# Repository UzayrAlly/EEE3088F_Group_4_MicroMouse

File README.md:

# EEE3088F_Group_4_MicroMouse
Micro-Mouse Sensing Subsystem

This repository contains the design documentation and testing procedures for the sensing subsystem of the Micro-Mouse project. The sensing subsystem serves as the "eyes" of the Micro-Mouse, detecting walls within a maze environment using infrared light and providing signals for navigation.

Contents:

Design Decisions: Discusses the initial circuit design, component selection, evaluation, and final design of the sensing module. It outlines the rationale behind component choices and design modifications.
Failure Management: Describes the processes implemented for failure management in PCB design, including Electrical Rule Check (ERC), Design Rule Check (DRC), Design for Manufacturing (DFM), troubleshooting design, and circuit testing.
System Integration and Interfacing: Details the interfacing specifications and connections of the sensing subsystem with other components of the Micro-Mouse project. Includes an interfacing diagram and table describing the connections.
Acceptance Testing: Provides a comprehensive overview of acceptance tests conducted to verify that all components function as expected and meet requirements and specifications. Each test is described along with its testing procedure and pass/fail criteria.

Repository Structure:

Data sheets: data sheets for components.
Schematics: Includes schematic diagrams of the initial and final circuit designs for the sensing module.
PCB production files: includes items needed to manufacture the board

Usage:

This repository serves as a reference for understanding the design and testing procedures of the Micro-Mouse sensing subsystem. Developers and engineers can utilize the documentation and schematics for further development or troubleshooting.

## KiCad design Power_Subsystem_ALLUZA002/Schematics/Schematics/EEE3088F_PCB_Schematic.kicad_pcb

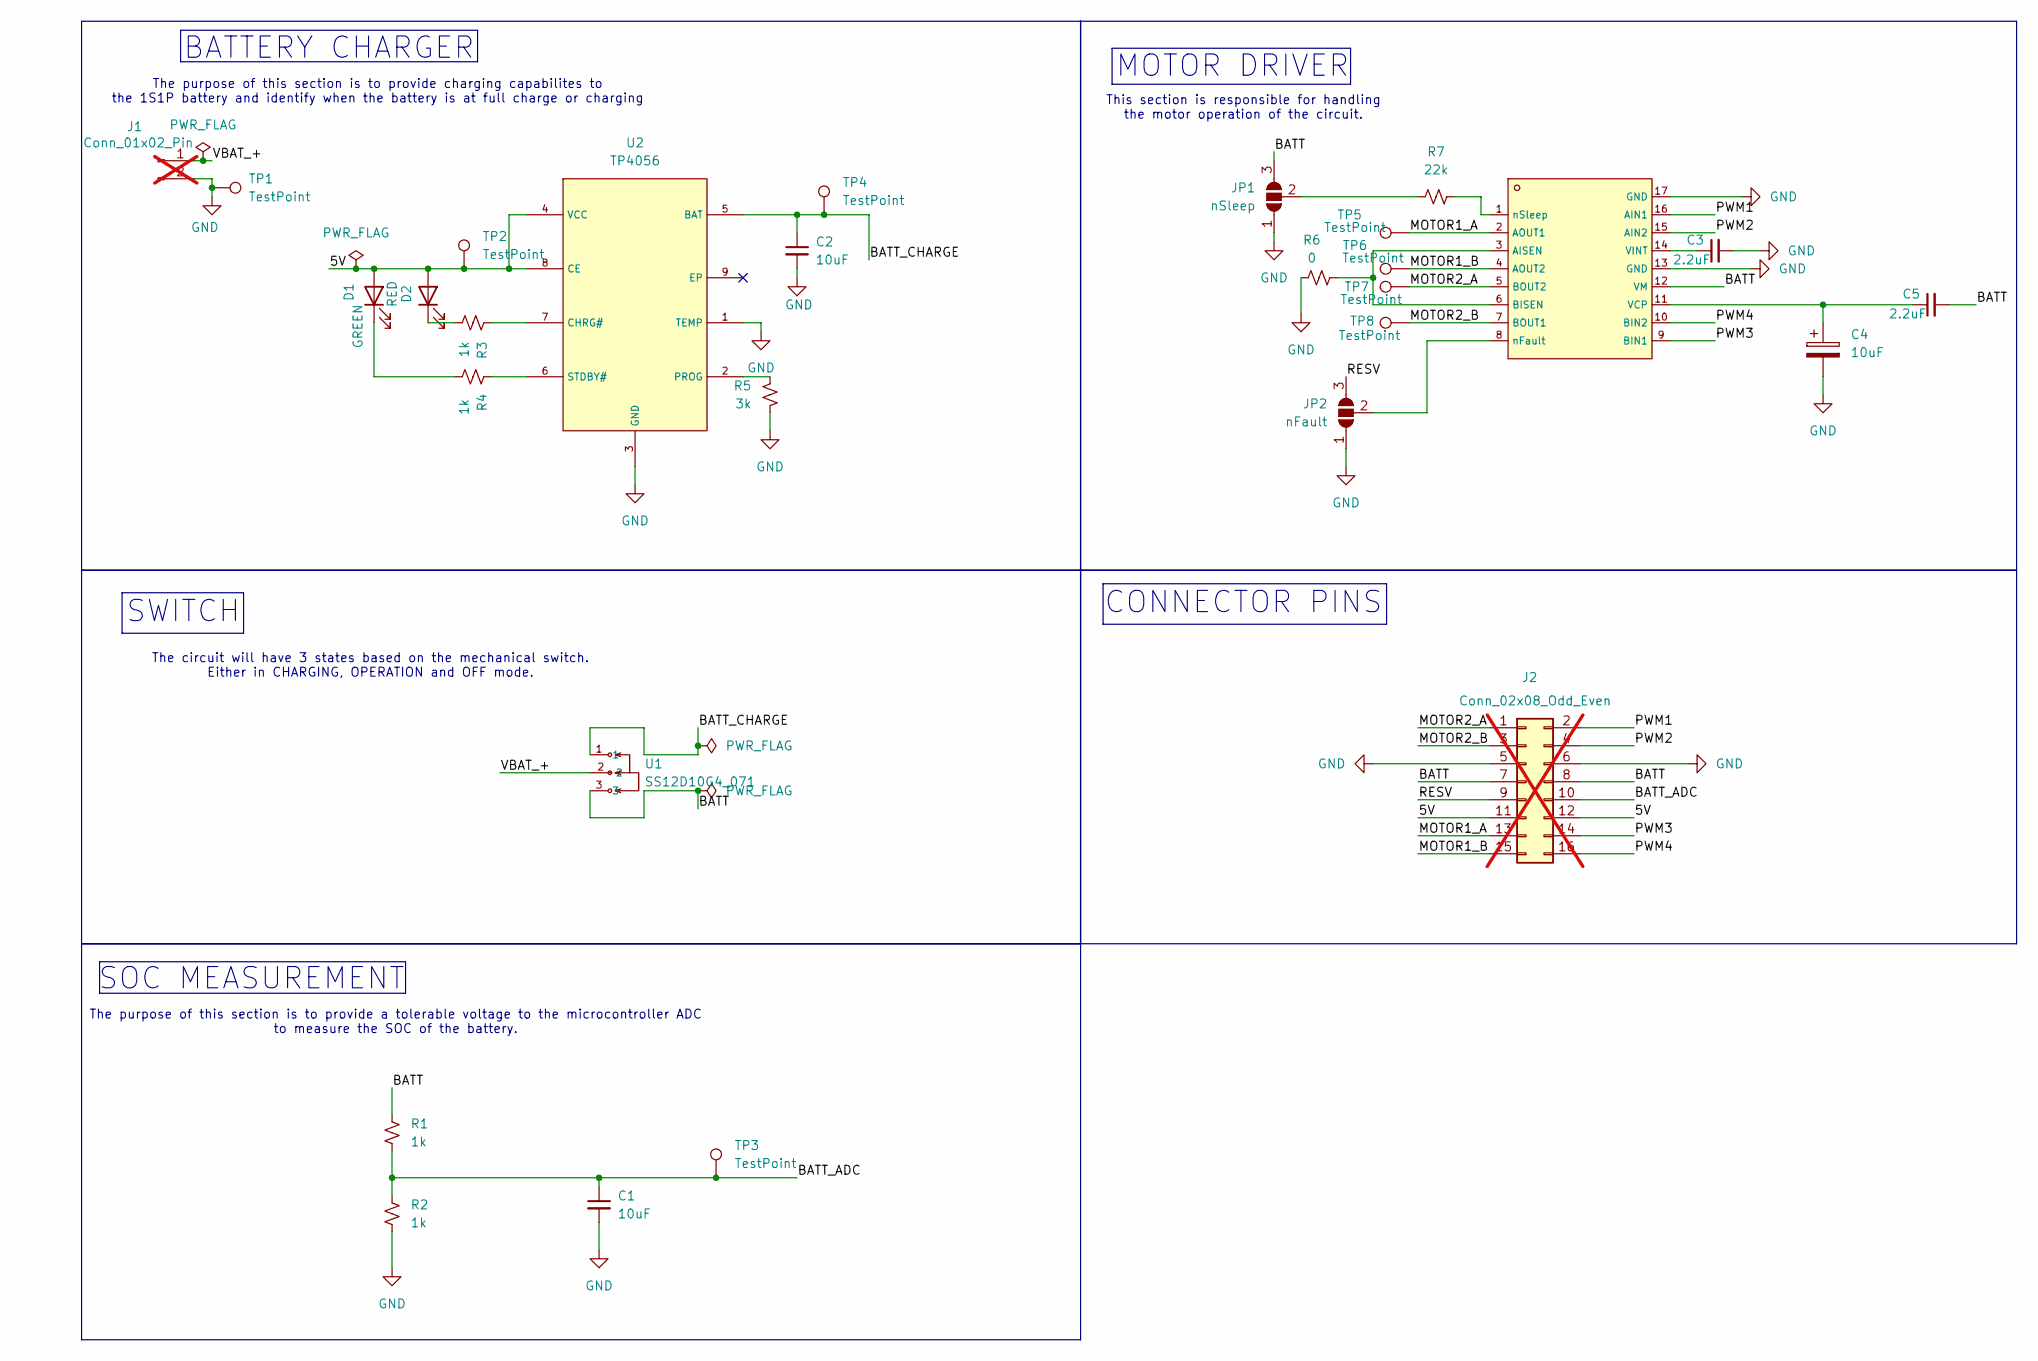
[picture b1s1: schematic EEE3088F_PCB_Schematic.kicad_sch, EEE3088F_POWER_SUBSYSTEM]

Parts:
C1, C2, C4: 10uF; C1206
C3, C5: 2.2uF; C0603
D1: GREEN; LED0805-R-RD
D2: RED; LED0603-RD
J1: Conn_01x02_Pin; PinHeader_1x02_P2.00mm_Vertical; not fitted
J2: Conn_02x08_Odd_Even; PinHeader_2x08_P2.54mm_Vertical; not fitted
JP1: nSleep; SolderJumper-3_P1.3mm_Open_RoundedPad1.0x1.5mm_NumberLabels
JP2: nFault; SolderJumper-3_P1.3mm_Open_RoundedPad1.0x1.5mm_NumberLabels
R1, R2, R3, R4: 1k; R0603
R5: 3k; R0603
R6: 0; R0603
R7: 22k; R0805
TP1, TP2, TP3, TP4, TP5, TP6, TP7, TP8: TestPoint; TestPoint_Loop_D1.80mm_Drill1.0mm_Beaded
U1: SS12D10G4_071; SW-TH_SHOU-HAN_SS12D10G4; LCSC C2887259
U2: TP4056; ESOP-8_L4.9-W3.9-P1.27-LS6.0-BL-EP; LCSC C16581
U3: DRV8833PWP; TSSOP-16_L5.0-W4.4-P0.65-LS6.4-BL-EP; LCSC C50506

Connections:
/5V: D1.2 (A), D2.2 (A), J2.11, J2.12, TP2.1, U2.4 (VCC), U2.8 (CE)
/BATT: C5.2, J2.7, J2.8, JP1.3 (B), R1.1, U1.3, U3.12 (VM)
/BATT_ADC: C1.1, J2.10, R1.2, R2.1, TP3.1
/BATT_CHARGE: C2.1, TP4.1, U1.1, U2.5 (BAT)
/MOTOR1_A: J2.13, TP5.1, U3.2 (AOUT1)
/MOTOR1_B: J2.15, TP6.1, U3.4 (AOUT2)
/MOTOR2_A: J2.1, TP7.1, U3.5 (BOUT2)
/MOTOR2_B: J2.3, TP8.1, U3.7 (BOUT1)
/PWM1: J2.2, U3.16 (AIN1)
/PWM2: J2.4, U3.15 (AIN2)
/PWM3: J2.14, U3.9 (BIN1)
/PWM4: J2.16, U3.10 (BIN2)
/RESV: J2.9, JP2.3 (B)
/VBAT_+: J1.1, U1.2
GND: C1.2, C2.2, C3.2, C4.2, J1.2, J2.5, J2.6, JP1.1 (A), JP2.1 (A), R2.2, R5.1, R6.1, TP1.1, U2.1 (TEMP), U2.3 (GND), U3.13 (GND), U3.17 (GND)
unnamed: D1.1 (K), R4.1
unnamed: D2.1 (K), R3.1
unnamed: JP1.2 (C), R7.1
unnamed: JP2.2 (C), U3.8 (nFault)
unnamed: R3.2, U2.7 (CHRG#)
unnamed: R5.2, U2.2 (PROG)
unnamed: R4.2, U2.6 (STDBY#)
unnamed: R6.2, U3.3 (AISEN), U3.6 (BISEN)
unnamed: C4.1, C5.1, U3.11 (VCP)
unnamed: C3.1, U3.14 (VINT)
unnamed: R7.2, U3.1 (nSleep)

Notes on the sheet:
MOTOR DRIVER
BATTERY CHARGER
SWITCH
The circuit will have 3 states based on the mechanical switch. Either in CHARGING, OPERATION and OFF mode.
SOC MEASUREMENT
The purpose of this section is to provide charging capabilites to the 1S1P battery and identify when the battery is at full charge or charging
The purpose of this section is to provide a tolerable voltage to the microcontroller ADC to measure the SOC of the battery.
CONNECTOR PINS
This section is responsible for handling the motor operation of the circuit.

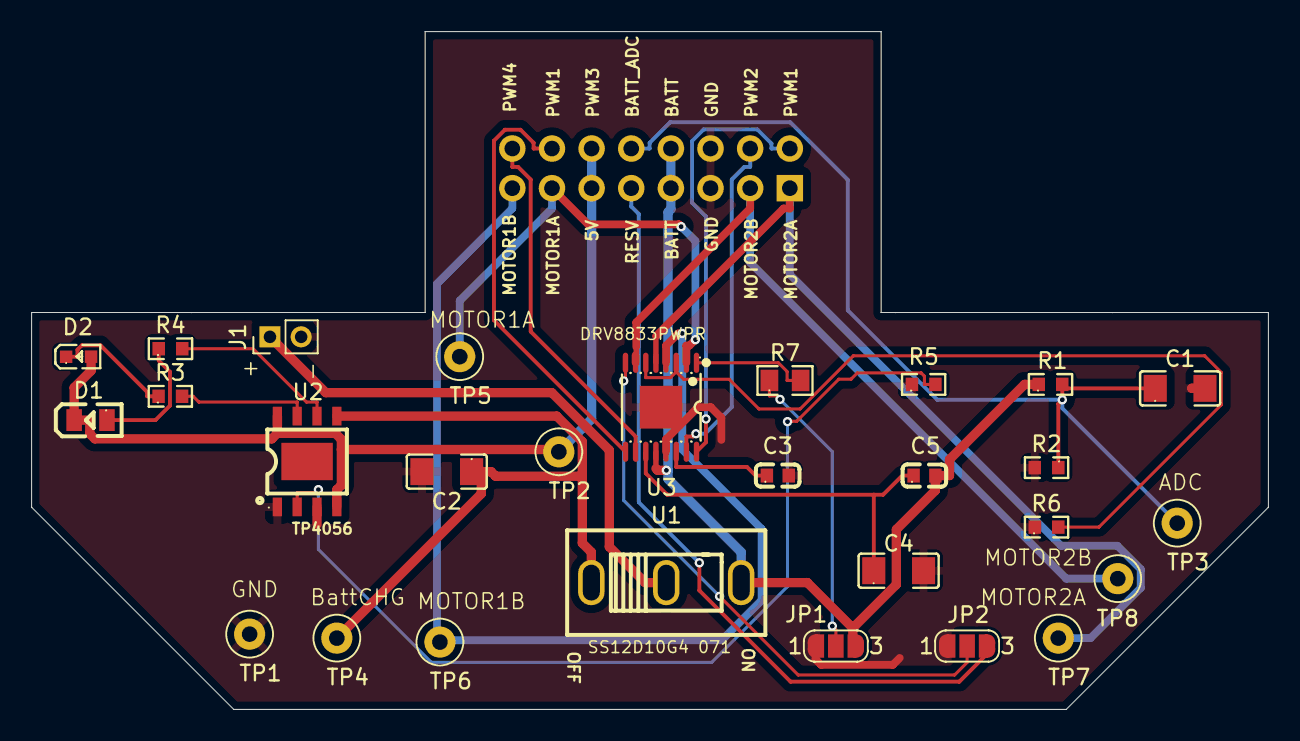
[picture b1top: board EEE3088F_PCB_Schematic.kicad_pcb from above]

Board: 2 copper layers, 79.2 x 43.4 mm, 29 parts (1 on the bottom side), 26 nets.

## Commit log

2024-04-21 added PCB production files produced by the JLCPCB.
2024-04-21 Production files for sensing PCB
2024-04-21 Create Sensing subsystem_DYXSAC001
2024-04-21 Create hi
2024-04-21 PCB production files generated by JLCPCB
2024-04-21 data sheets for calculations.
2024-04-21 data_sheets added
